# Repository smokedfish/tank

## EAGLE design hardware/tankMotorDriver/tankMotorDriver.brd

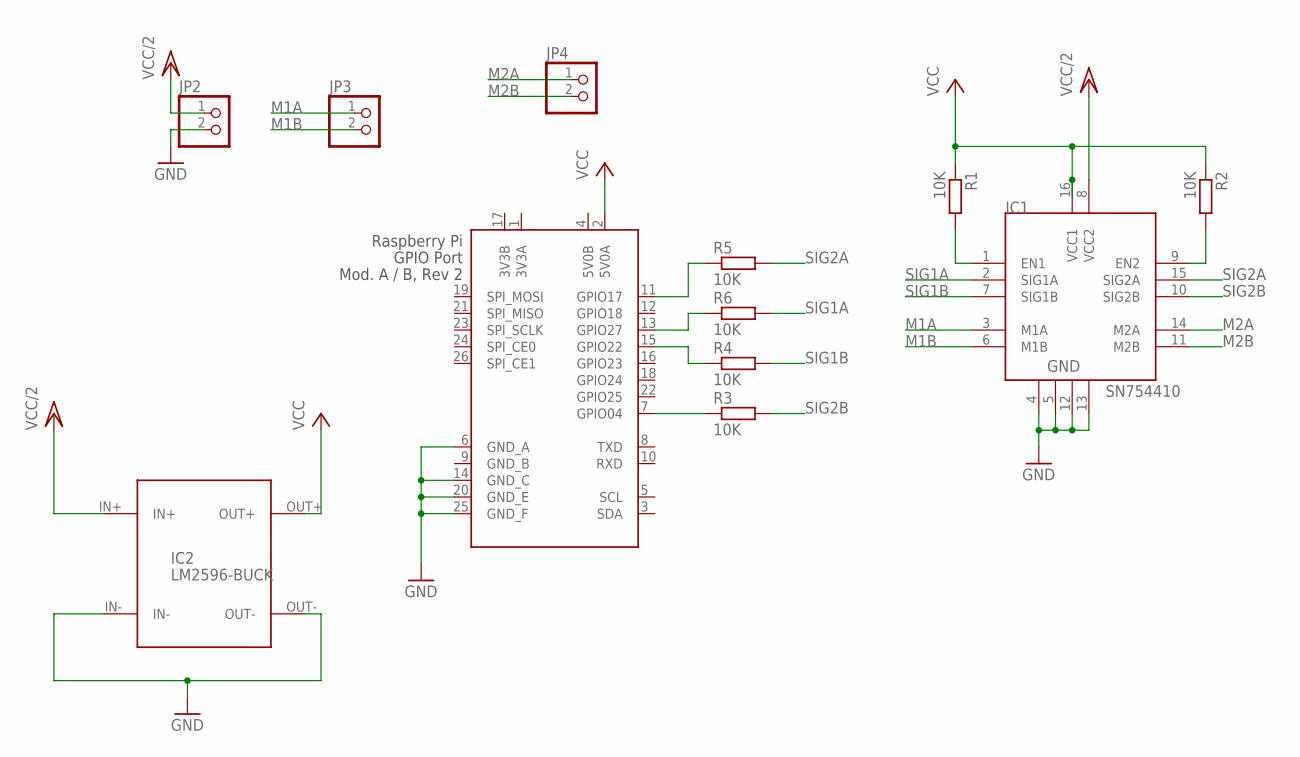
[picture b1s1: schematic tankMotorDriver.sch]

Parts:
IC1: SN754410; DIP16
IC2: LM2596-BUCK
JP2, JP3, JP4: PINHD-1X2; 1X02
R1, R2, R3, R4, R5, R6: 10K; 0207/10
X1: RASPI_GPIO_AB#_PIN; RASPI_GPIO_AB_PIN

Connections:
3V3A: X1.1 (3V3A)
3V3B: X1.17 (3V3B)
5V0B: X1.4 (5V0B)
GND: IC1.4, IC1.5, IC1.12, IC1.13, IC2.IN-, IC2.OUT-, JP2.2, X1.6 (GND_A), X1.14 (GND_C), X1.20 (GND_E), X1.25 (GND_F)
GND_B: X1.9 (GND_B)
M1A: IC1.3 (M1A), JP3.1
M1B: IC1.6 (M1B), JP3.2
M2A: IC1.14 (M2A), JP4.1
M2B: IC1.11 (M2B), JP4.2
unnamed: IC1.1 (EN1), R1.2
unnamed: IC1.9 (EN2), R2.2
unnamed: R3.1, X1.7 (GPIO04)
unnamed: R5.1, X1.11 (GPIO17)
unnamed: R6.1, X1.13 (GPIO27)
unnamed: R4.1, X1.15 (GPIO22)
SIG1A: IC1.2 (SIG1A), R6.2
SIG1B: IC1.7 (SIG1B), R4.2
SIG2A: IC1.15 (SIG2A), R5.2
SIG2B: IC1.10 (SIG2B), R3.2
VCC: IC1.16 (VCC1), IC2.OUT+, R1.1, R2.1, X1.2 (5V0A)
VCC/2: IC1.8 (VCC2), IC2.IN+, JP2.1

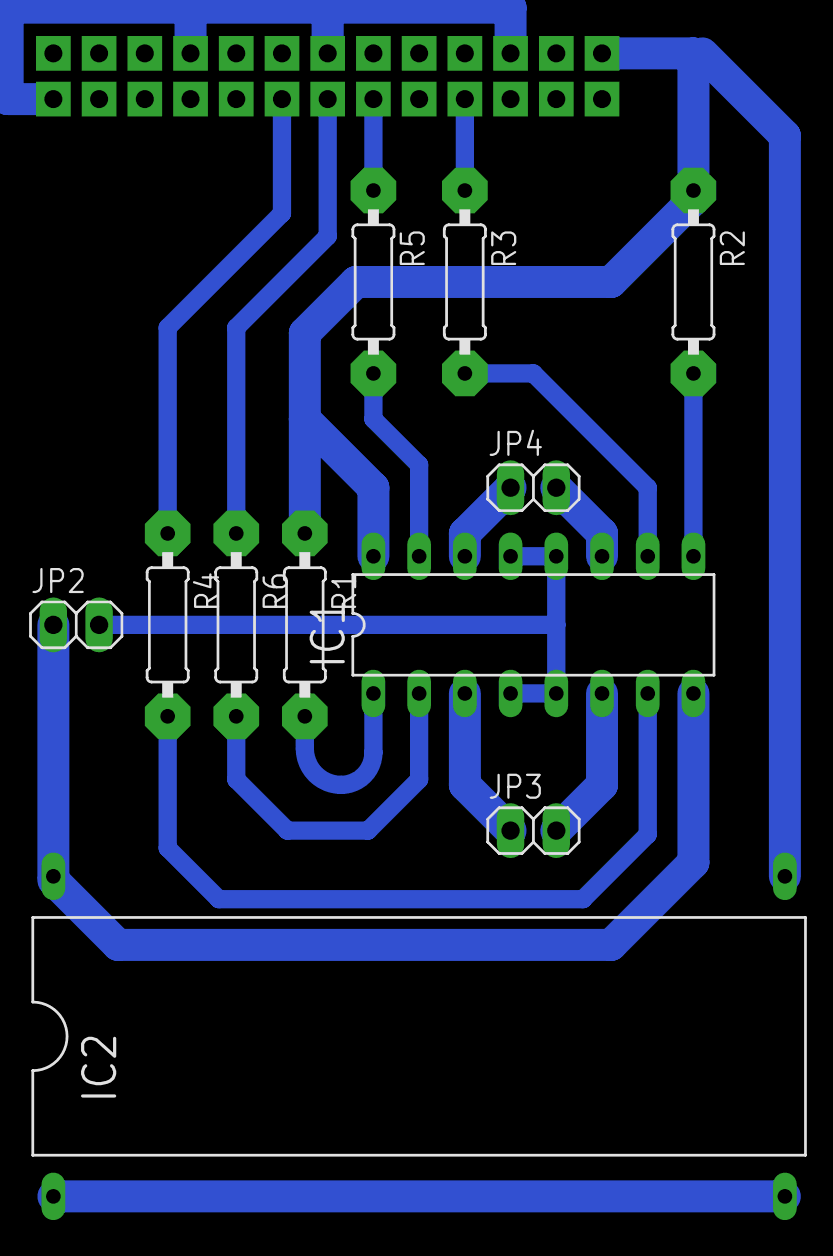
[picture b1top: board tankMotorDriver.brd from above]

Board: 2 copper layers, 12 parts (1 on the bottom side), 17 nets.

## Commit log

2015-07-10 :octocat: Added .gitattributes & .gitignore files
2015-07-10 Initial version
2015-07-10 2nd cost reduced version
2015-07-10 Further cost reductions
    Had this version manufactured by razorlab
2015-07-10 Initial source code
    Source code from
    http://www.seewald.at/en/2014/10/toycollect
2015-07-10 initial hardware version
